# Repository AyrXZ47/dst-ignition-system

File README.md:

# 🚀 DST Ignition System

A solid-state, remote ignition system designed for experimental rocketry. Built for the Dragons Space Team to safely and reliably ignite rocket motors (like Estes Viking) using electronic matches.

## 🧠 System Architecture
* **Microcontroller:** Raspberry Pi Pico (RP2040)
* **Firmware:** Rust 🦀 with Embassy — **planned, not implemented yet** (see [Hardware status](#-hardware-status))
* **Telemetry & Comms:** LoRa (SX1278 RA-02, single transceiver — TX/RX role is firmware-side, half-duplex)
* **Power Switching:** Logic-Level N-Channel MOSFET (AOD4184A)

## 📂 Repository Structure
* `/hardware/`: KiCad project files (Schematics and PCB layouts).
* `/src/`: Rust source code for the RP2040 firmware.
* `/docs/`: Pinout diagrams, component datasheets, and operation manuals.

## 🛠️ Getting Started
### Firmware (Rust)
⚠️ **Not available yet.** The `src/` directory is empty: the Rust/Embassy firmware is planned but has not been written. The steps below are reserved for when it lands:

1. Install Rust and the `thumbv6m-none-eabi` target:
   `rustup target add thumbv6m-none-eabi`
2. Install `elf2uf2-rs` for easy flashing:
   `cargo install elf2uf2-rs --locked`
3. Build and run: `cargo run --release`

### Hardware
Open the project in KiCad 10.x (KiCad 9.x also fine) located in the `/hardware/` directory.

## 📋 Hardware status

Schematics and PCB live in `/hardware/Kicad/ignition-system/`. Current status
(wave 3, in progress — see [`docs/design-notes.md`](docs/design-notes.md) for
the full design reference):

* **Schematic:** RP2040 (Pico) + TP4056 Li-ion charger (TEMP via external NTC 10k B3950, TH1) + AOD4184A N-MOSFET ignition switch + SX1278 RA-02 socket (2× 1×08 headers: SPI + control rows) + I2C display + status LEDs + master power switch SW3 (battery → SW3 → VSYS; the pack charges with the board off). ERC: 0 errors / 0 warnings.
* **PCB:** placement in progress, **not routed** (agentes solo verifican con kicad-cli). DRC findings pending wave-3 fixes; see design-notes §5.
* **Firmware:** `src/` is empty; no Rust/Embassy code exists yet.
* **Next:** wave 2 SPICE validation of the MOSFET gate margin (3.3V vs Vto 2.61V).

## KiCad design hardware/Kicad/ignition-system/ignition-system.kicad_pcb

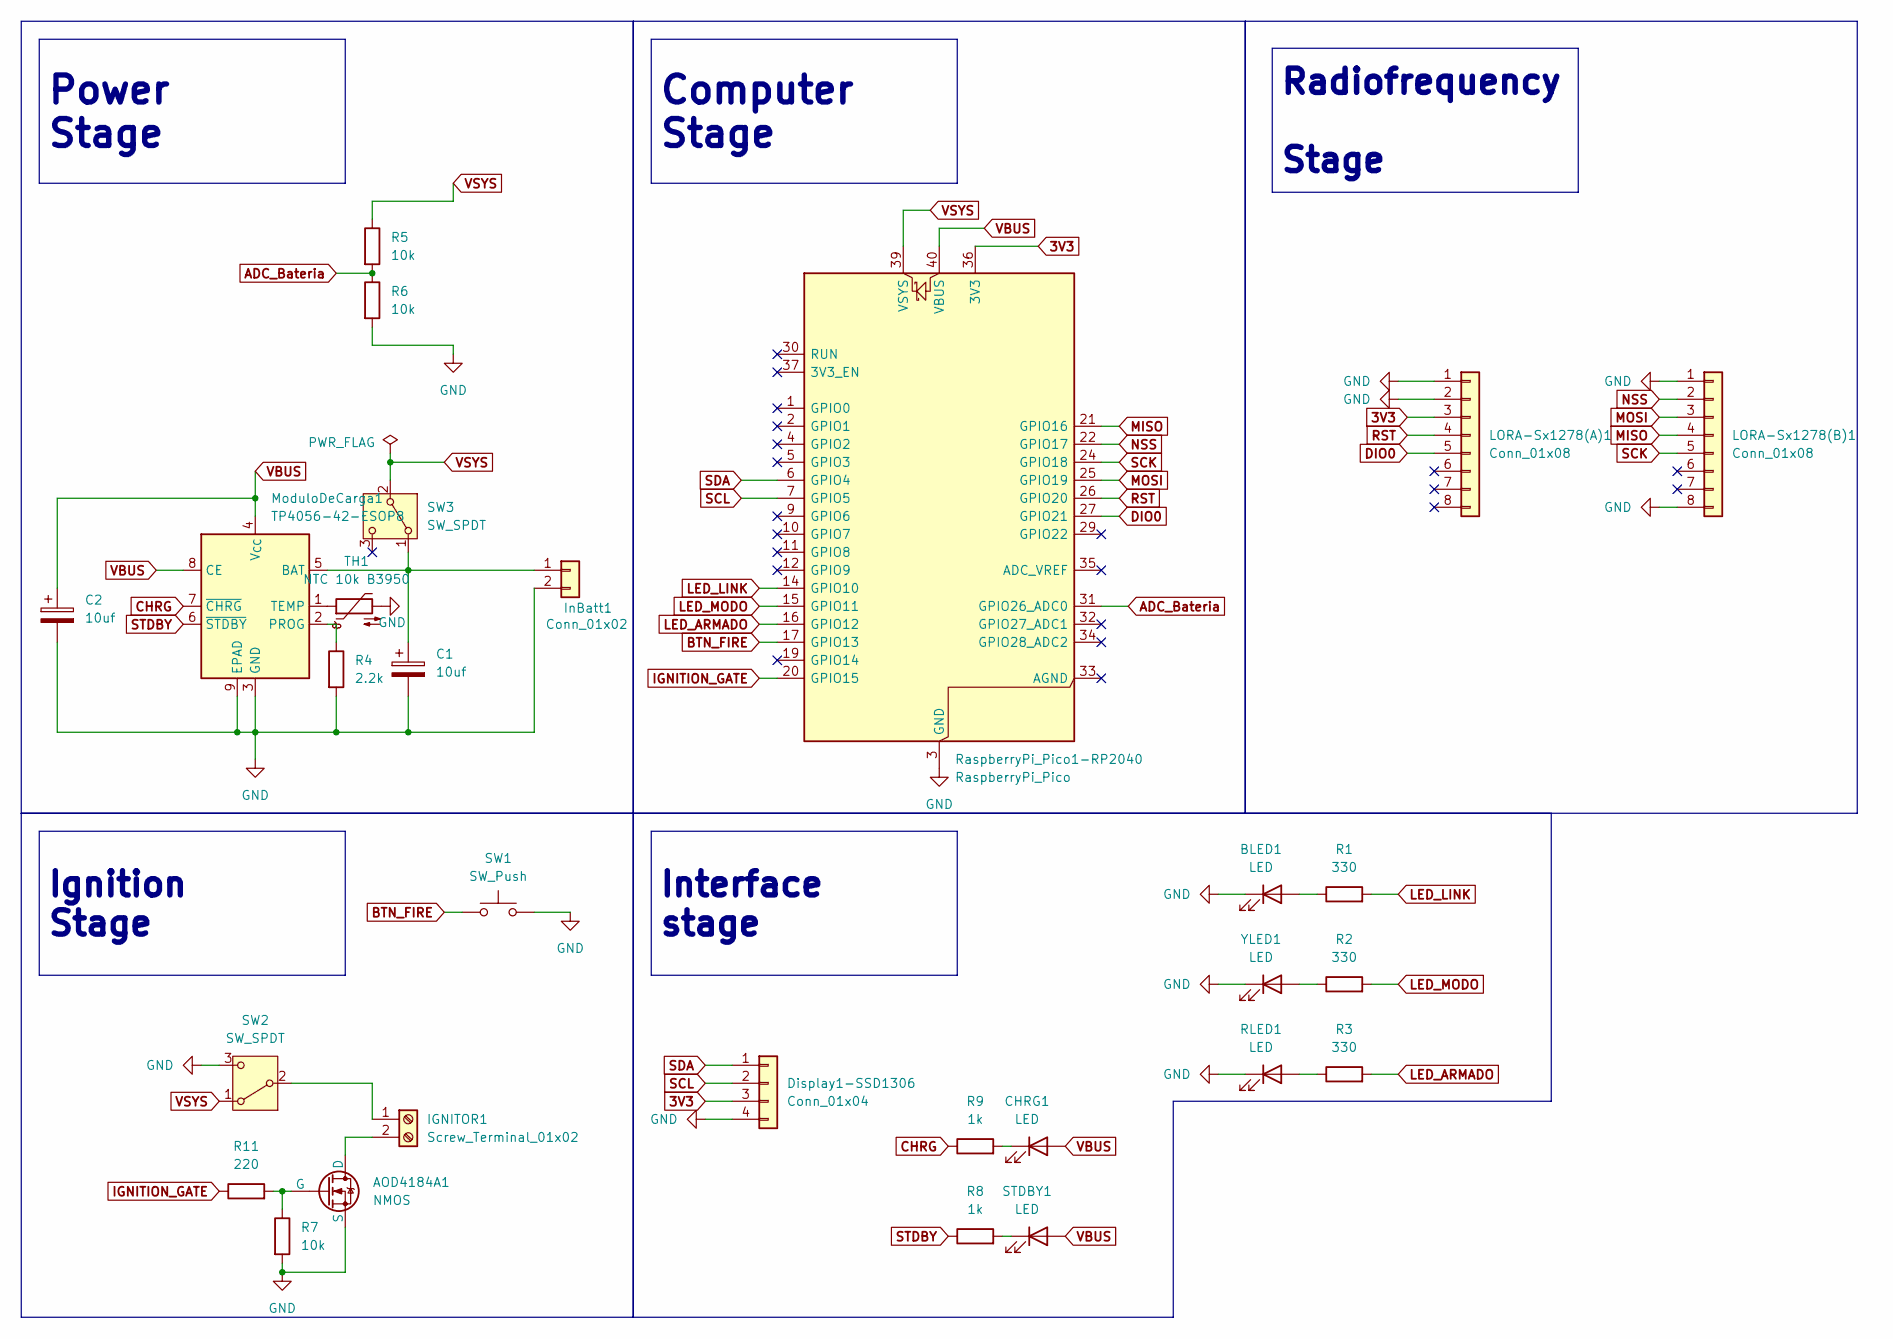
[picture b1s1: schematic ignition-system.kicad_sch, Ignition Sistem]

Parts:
AOD4184A1: NMOS; TO-252-2
BLED1: LED; LED_0805_2012Metric
C1, C2: 10uf; C_0805_2012Metric
CHRG1: LED; LED_0805_2012Metric
Display1-SSD1306: Conn_01x04; PinHeader_1x04_P2.54mm_Vertical
IGNITOR1: Screw_Terminal_01x02; TerminalBlock_MaiXu_MX126-5.0-02P_1x02_P5.00mm
InBatt1: Conn_01x02; JST_PH_S2B-PH-K_1x02_P2.00mm_Horizontal
LORA-Sx1278(A)1, LORA-Sx1278(B)1: Conn_01x08; PinHeader_1x08_P2.54mm_Vertical
ModuloDeCarga1: TP4056-42-ESOP8; SOIC-8-1EP_3.9x4.9mm_P1.27mm_EP2.41x3.3mm_ThermalVias
R1, R2, R3: 330; R_0805_2012Metric
R4: 2.2k; R_0805_2012Metric
R5, R6, R7: 10k; R_0805_2012Metric
R8, R9: 1k; R_0805_2012Metric
R11: 220; R_0805_2012Metric
RLED1: LED; LED_0805_2012Metric
RaspberryPi_Pico1-RP2040: RaspberryPi_Pico; RaspberryPi_Pico_Common_Unspecified
STDBY1: LED; LED_0805_2012Metric
SW1: SW_Push; JST_PH_S2B-PH-K_1x02_P2.00mm_Horizontal
SW2, SW3: SW_SPDT; SW_E-Switch_EG1224_SPDT_Angled
TH1: NTC 10k B3950; JST_PH_S2B-PH-K_1x02_P2.00mm_Horizontal
YLED1: LED; LED_0805_2012Metric

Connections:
3V3: Display1-SSD1306.3, LORA-Sx1278(A)1.3, RaspberryPi_Pico1-RP2040.36 (3V3)
ADC_Bateria: R5.2, R6.1, RaspberryPi_Pico1-RP2040.31 (GPIO26_ADC0)
BTN_FIRE: RaspberryPi_Pico1-RP2040.17 (GPIO13), SW1.1
CHRG: ModuloDeCarga1.7 (~CHRG), R9.1
DIO0: LORA-Sx1278(A)1.5, RaspberryPi_Pico1-RP2040.27 (GPIO21)
GND: AOD4184A1.3 (S), BLED1.1 (K), C1.2, C2.2, Display1-SSD1306.4, InBatt1.2, LORA-Sx1278(A)1.1, LORA-Sx1278(A)1.2, LORA-Sx1278(B)1.1, LORA-Sx1278(B)1.8, ModuloDeCarga1.3 (GND), ModuloDeCarga1.9 (EPAD), R4.2, R6.2, R7.2, RLED1.1 (K), RaspberryPi_Pico1-RP2040.3 (GND), RaspberryPi_Pico1-RP2040.8 (GND), RaspberryPi_Pico1-RP2040.13 (GND), RaspberryPi_Pico1-RP2040.18 (GND), RaspberryPi_Pico1-RP2040.23 (GND), RaspberryPi_Pico1-RP2040.28 (GND), RaspberryPi_Pico1-RP2040.38 (GND), SW1.2, SW2.3 (C), TH1.2, YLED1.1 (K)
IGNITION_GATE: R11.1, RaspberryPi_Pico1-RP2040.20 (GPIO15)
LED_ARMADO: R3.2, RaspberryPi_Pico1-RP2040.16 (GPIO12)
LED_LINK: R1.2, RaspberryPi_Pico1-RP2040.14 (GPIO10)
LED_MODO: R2.2, RaspberryPi_Pico1-RP2040.15 (GPIO11)
MISO: LORA-Sx1278(B)1.4, RaspberryPi_Pico1-RP2040.21 (GPIO16)
MOSI: LORA-Sx1278(B)1.3, RaspberryPi_Pico1-RP2040.25 (GPIO19)
NSS: LORA-Sx1278(B)1.2, RaspberryPi_Pico1-RP2040.22 (GPIO17)
unnamed: AOD4184A1.1 (D), IGNITOR1.2
unnamed: AOD4184A1.2 (G), R7.1, R11.2
unnamed: BLED1.2 (A), R1.1
unnamed: CHRG1.1 (K), R9.2
unnamed: IGNITOR1.1, SW2.2 (B)
unnamed: C1.1, InBatt1.1, ModuloDeCarga1.5 (BAT), SW3.1 (A)
unnamed: ModuloDeCarga1.2 (PROG), R4.1
unnamed: ModuloDeCarga1.1 (TEMP), TH1.1
unnamed: R3.1, RLED1.2 (A)
unnamed: R8.2, STDBY1.1 (K)
unnamed: R2.1, YLED1.2 (A)
RST: LORA-Sx1278(A)1.4, RaspberryPi_Pico1-RP2040.26 (GPIO20)
SCK: LORA-Sx1278(B)1.5, RaspberryPi_Pico1-RP2040.24 (GPIO18)
SCL: Display1-SSD1306.2, RaspberryPi_Pico1-RP2040.7 (GPIO5)
SDA: Display1-SSD1306.1, RaspberryPi_Pico1-RP2040.6 (GPIO4)
STDBY: ModuloDeCarga1.6 (~STDBY), R8.1
VBUS: C2.1, CHRG1.2 (A), ModuloDeCarga1.4 (V_{CC}), ModuloDeCarga1.8 (CE), RaspberryPi_Pico1-RP2040.40 (VBUS), STDBY1.2 (A)
VSYS: R5.1, RaspberryPi_Pico1-RP2040.39 (VSYS), SW2.1 (A), SW3.2 (B)

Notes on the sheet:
Radiofrequency Stage
Interface stage
Computer Stage
Power Stage
Ignition Stage

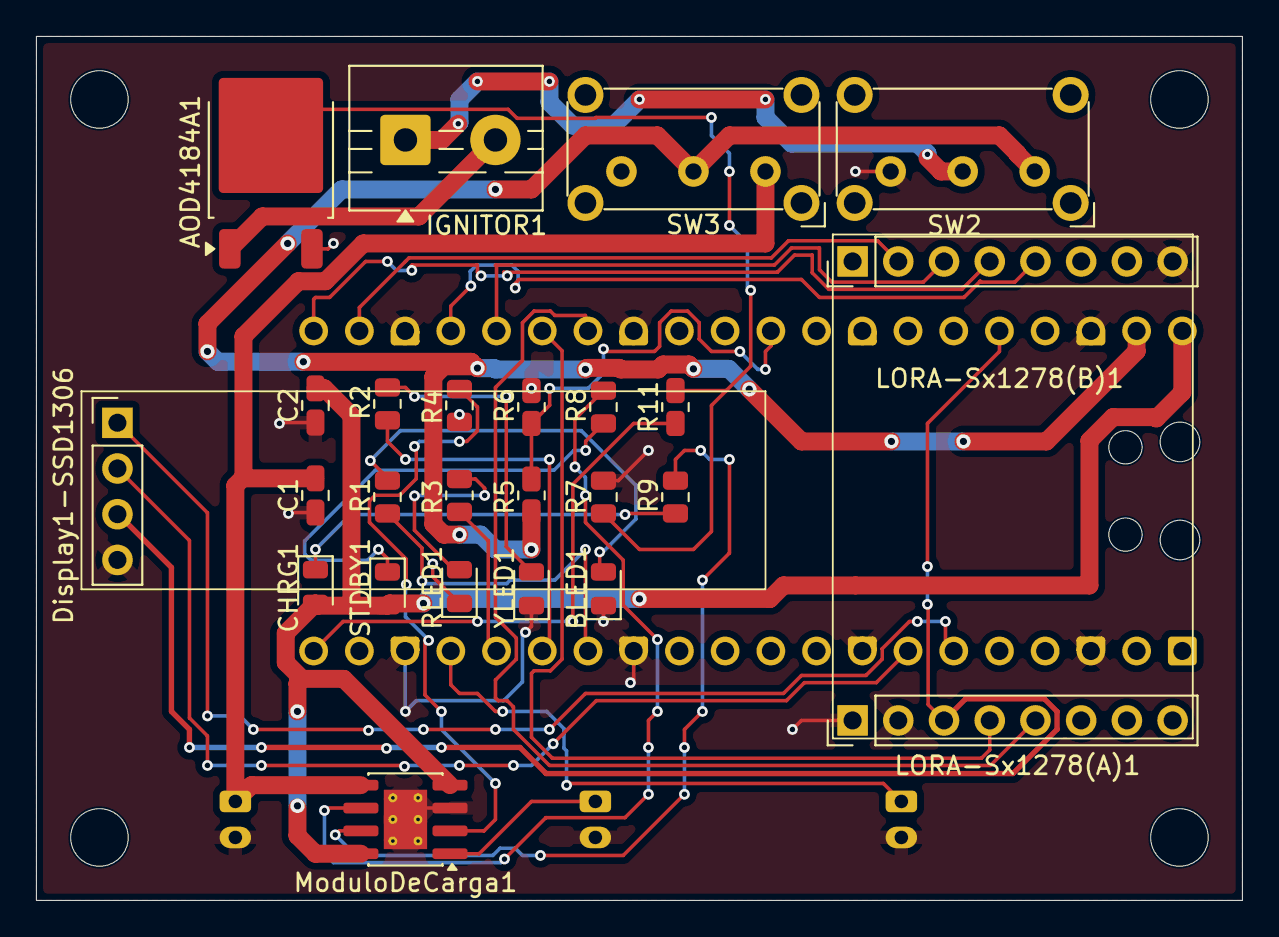
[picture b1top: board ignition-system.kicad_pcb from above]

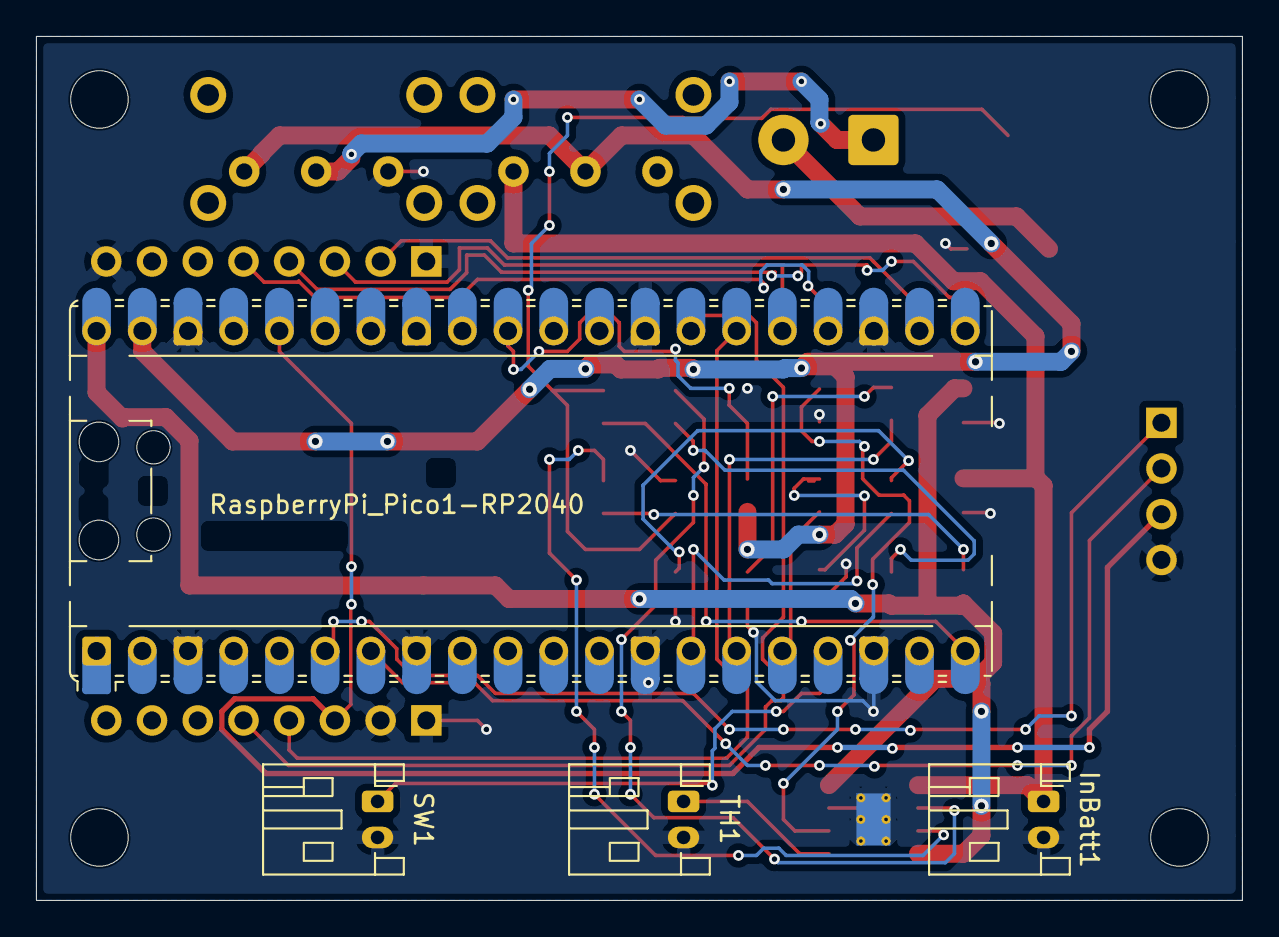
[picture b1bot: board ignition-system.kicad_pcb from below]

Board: 2 copper layers, 67.0 x 48.0 mm, 29 parts (4 on the bottom side), 31 nets.

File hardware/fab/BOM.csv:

"Refs","Value","Footprint","Qty","DNP"
"AOD4184A1","NMOS","Package_TO_SOT_SMD:TO-252-2","1",""
"BLED1","LED","LED_SMD:LED_0805_2012Metric","1",""
"C1","10uf","Capacitor_SMD:C_0805_2012Metric","1",""
"C2","10uf","Capacitor_SMD:C_0805_2012Metric","1",""
"CHRG1","LED","LED_SMD:LED_0805_2012Metric","1",""
"Display1-SSD1306","Conn_01x04","Connector_PinHeader_2.54mm:PinHeader_1x04_P2.54mm_Vertical","1",""
"IGNITOR1","Screw_Terminal_01x02","TerminalBlock:TerminalBlock_MaiXu_MX126-5.0-02P_1x02_P5.00mm","1",""
"InBatt1","Conn_01x02","Connector_JST:JST_PH_S2B-PH-K_1x02_P2.00mm_Horizontal","1",""
"LORA-Sx1278(A)1","Conn_01x08","Connector_PinHeader_2.54mm:PinHeader_1x08_P2.54mm_Vertical","1",""
"LORA-Sx1278(B)1","Conn_01x08","Connector_PinHeader_2.54mm:PinHeader_1x08_P2.54mm_Vertical","1",""
"ModuloDeCarga1","TP4056-42-ESOP8","Package_SO:SOIC-8-1EP_3.9x4.9mm_P1.27mm_EP2.41x3.3mm_ThermalVias","1",""
"R1","330","Resistor_SMD:R_0805_2012Metric","1",""
"R2","330","Resistor_SMD:R_0805_2012Metric","1",""
"R3","330","Resistor_SMD:R_0805_2012Metric","1",""
"R4","2.2k","Resistor_SMD:R_0805_2012Metric","1",""
"R5","10k","Resistor_SMD:R_0805_2012Metric","1",""
"R6","10k","Resistor_SMD:R_0805_2012Metric","1",""
"R7","10k","Resistor_SMD:R_0805_2012Metric","1",""
"R8","1k","Resistor_SMD:R_0805_2012Metric","1",""
"R9","1k","Resistor_SMD:R_0805_2012Metric","1",""
"R11","220","Resistor_SMD:R_0805_2012Metric","1",""
"RaspberryPi_Pico1-RP2040","RaspberryPi_Pico","Module:RaspberryPi_Pico_Common_Unspecified","1",""
"RLED1","LED","LED_SMD:LED_0805_2012Metric","1",""
"STDBY1","LED","LED_SMD:LED_0805_2012Metric","1",""
"SW1","SW_Push","Connector_JST:JST_PH_S2B-PH-K_1x02_P2.00mm_Horizontal","1",""
"SW2","SW_SPDT","Button_Switch_THT:SW_E-Switch_EG1224_SPDT_Angled","1",""
"SW3","SW_SPDT","Button_Switch_THT:SW_E-Switch_EG1224_SPDT_Angled","1",""
"TH1","NTC 10k B3950","Connector_JST:JST_PH_S2B-PH-K_1x02_P2.00mm_Horizontal","1",""
"YLED1","LED","LED_SMD:LED_0805_2012Metric","1",""

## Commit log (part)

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2026-05-09 docs: actualizacion de README para el nuevo sistema RP2040
2026-05-09 feat: añadir componentes al esquematico y modelo spice a NMOS
2026-05-09 feat: nuevos componentes y estructura con net labels
2026-05-09 docs: añadir esquematico en pdf

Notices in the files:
README.md:
License: Apache 2.0
Hardware License: CERN-OHL-P-2.0
